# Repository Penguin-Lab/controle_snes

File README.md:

# controle_snes
Esse controle parecido com o de SNES (mas com analógico) foi projetado para ser usado na disciplina de Sistemas Digitais da Engenharia Elétrica. Ele envia a leitura de todos os botões e do joystick para uma FPGA de uma placa de desenvolvimento Basys 2 da Digilent. Essa comunicação é feita por UART.

Este controle foi utilizado em um trabalho para o comando de sprites do Mario Bros. em um monitor VGA.

# Estrutura física
A estrutura física do controle é composta por duas peças da carcaça e 7 botões coloridos. Esse conjunto esconde a placa de circuito impresso desenvolvida e o módulo joystick.
As peças projetadas em 3D foram impressas utilizando PLA e podem ser encontradas na pasta [Pecas_3d](https://github.com/Penguin-Lab/controle_snes/tree/main/Pecas_3d) deste projeto.

## Placas de circuito impresso
No projeto, foi desenvolvida uma placa de circuito para que um ATMEGA328p (arduino) pudesse ler os sinais do controle e enviá-los por UART para a FPGA.

O esquemático e o board do Eagle (v7.7.0) deste projeto podem ser encontrados na pasta [Placa](https://github.com/Penguin-Lab/controle_snes/tree/main/Placa). Lá também é possível encontrar o PDF para que seja impresso o projeto diretamente, sem precisar abrir o board no Eagle.

## Componentes eletrônicos
Os componentes eletrônicos utilizados para a confecção da placa são:
* 8x resistor 10k
* 2x resistor 150R
* 2x resistor 120R
* 7x push-buttons
* 1x LED vermelho 5mm
* 1x BUZZER
* 2x capacitores 22pF
* 1x cristal de clock 16MHz
* 1x soquete de 28 pinos
* 1x ATMEGA328p
* 1x módulo joystick
* 1x pinheader 6x1 macho 90 graus
* 1x pinheader 5x1 femea 90 graus

# Software
Na pasta [Codes](https://github.com/Penguin-Lab/controle_snes/tree/main/Codes), há o código de programação do arduino e da FPGA.

# Vídeo de teste
Caso queira ver um teste com o sistema funcionando, e com a implementação ainda do som do jogo sendo tocado no buzzer do controle, adicionamos um vídeo no [canal do Lab](https://www.youtube.com/channel/UCKsklKPVTsWEkaLD-hVZmng)!

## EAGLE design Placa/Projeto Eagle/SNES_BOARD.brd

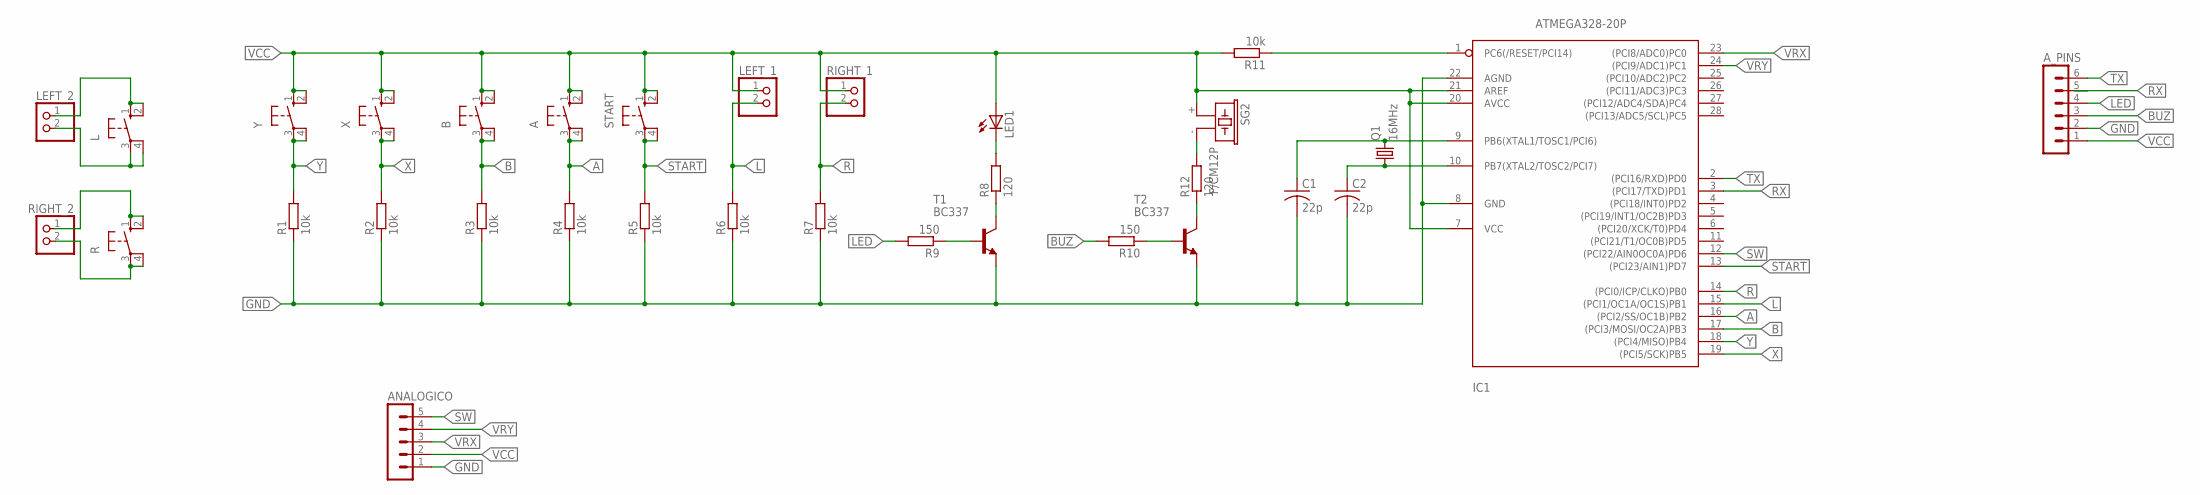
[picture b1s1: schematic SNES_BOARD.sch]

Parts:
A: 10-XX; B3F-10XX
ANALOGICO: MA05-1
A_PINS: MA06-1
B: 10-XX; B3F-10XX
C1, C2: 22p; C025-025X050
IC1: ATMEGA328-20P; DIL28-3
L: 10-XX; B3F-10XX
LED1: LED5MM
LEFT_1, LEFT_2: PINHD-1X2; 1X02
Q1: 16MHz; HC49U-V
R: 10-XX; B3F-10XX
R1, R2, R3, R4, R5, R6, R7, R11: 10k; 0207/12
R8, R12: 120; 0207/12
R9, R10: 150; 0207/12
RIGHT_1, RIGHT_2: PINHD-1X2; 1X02
SG2: F/CM12P
START: 10-XX; B3F-10XX
T1, T2: BC337; TO92
X: 10-XX; B3F-10XX
Y: 10-XX; B3F-10XX

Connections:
A: A.3, A.4 (P1), IC1.16 ((PCI2/SS/OC1B)PB2), R4.2
B: B.3, B.4 (P1), IC1.17 ((PCI3/MOSI/OC2A)PB3), R3.2
BUZ: A_PINS.3, R10.2
GND: ANALOGICO.1, A_PINS.2, C1.2, C2.2, IC1.8 (GND), IC1.22 (AGND), R1.1, R2.1, R3.1, R4.1, R5.1, R6.1, R7.1, T1.1 (E), T2.1 (E)
L: IC1.15 ((PCI1/OC1A/OC1S)PB1), LEFT_1.2, R6.2
LED: A_PINS.4, R9.2
unnamed: LED1.K (C), R8.2
unnamed: L.1 (S), L.2 (S1), LEFT_2.1
unnamed: L.3, L.4 (P1), LEFT_2.2
unnamed: R.1 (S), R.2 (S1), RIGHT_2.1
unnamed: R.3, R.4 (P1), RIGHT_2.2
unnamed: R8.1, T1.3 (C)
unnamed: R9.1, T1.2 (B)
unnamed: R12.2, SG2.- (2)
unnamed: R10.1, T2.2 (B)
unnamed: IC1.1 (PC6(/RESET/PCI14)), R11.1
unnamed: C1.1, IC1.9 (PB6(XTAL1/TOSC1/PCI6)), Q1.2
unnamed: C2.1, IC1.10 (PB7(XTAL2/TOSC2/PCI7)), Q1.1
unnamed: R12.1, T2.3 (C)
R: IC1.14 ((PCI0/ICP/CLKO)PB0), R7.2, RIGHT_1.2
RX: A_PINS.5, IC1.3 ((PCI17/TXD)PD1)
START: IC1.13 ((PCI23/AIN1)PD7), R5.2, START.3, START.4 (P1)
SW: ANALOGICO.5, IC1.12 ((PCI22/AIN0OC0A)PD6)
TX: A_PINS.6, IC1.2 ((PCI16/RXD)PD0)
VCC: A.1 (S), A.2 (S1), ANALOGICO.2, A_PINS.1, B.1 (S), B.2 (S1), IC1.7 (VCC), IC1.20 (AVCC), IC1.21 (AREF), LED1.A, LEFT_1.1, R11.2, RIGHT_1.1, SG2.+ (1), START.1 (S), START.2 (S1), X.1 (S), X.2 (S1), Y.1 (S), Y.2 (S1)
VRX: ANALOGICO.3, IC1.23 ((PCI8/ADC0)PC0)
VRY: ANALOGICO.4, IC1.24 ((PCI9/ADC1)PC1)
X: IC1.19 ((PCI5/SCK)PB5), R2.2, X.3, X.4 (P1)
Y: IC1.18 ((PCI4/MISO)PB4), R1.2, Y.3, Y.4 (P1)

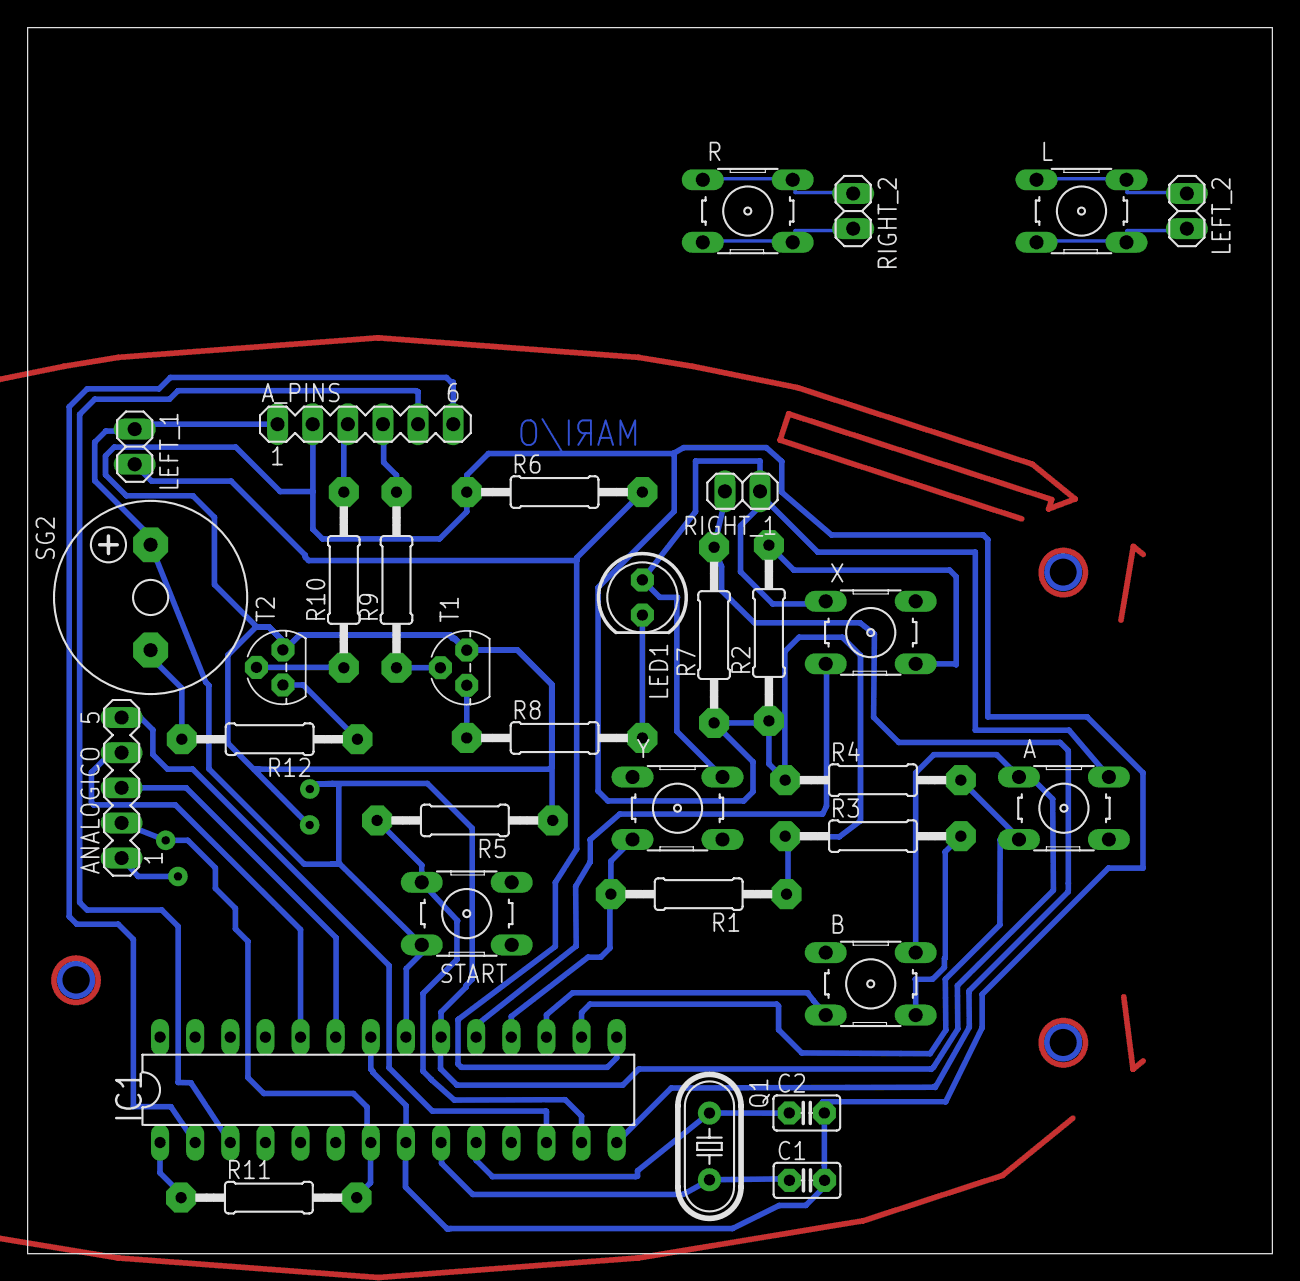
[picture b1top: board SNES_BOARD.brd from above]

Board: 2 copper layers, 90.0 x 88.7 mm, 33 parts (0 on the bottom side), 29 nets.

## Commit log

2021-12-20 Add files via upload
    peças 3d do controle
2021-12-20 Add files via upload
    fotos, imagens do controle e sprites do mario
2021-12-20 Add files via upload
    sprites do mario e foto da basys2
2021-12-20 Add files via upload
    código para vhdl (basys 2) e arduino (controle)
2021-12-20 Update README.md
    explicação dos códigos
2021-12-20 Add files via upload
    melhor vista dos pinos do controle
2021-12-20 Add files via upload
    esquemático, board e arquivos pdf da placa
2021-12-20 Update README.md
    descrição geral
